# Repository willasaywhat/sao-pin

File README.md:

# SAO Pin

Quick board to provide power to an SAO without a badge. Hot glue a pin or lanyard clip on the back and wear it with pride.

Note: This is currently untested and probably doesn't work. Also uses both the DigiKey and Sparkfun libraries.

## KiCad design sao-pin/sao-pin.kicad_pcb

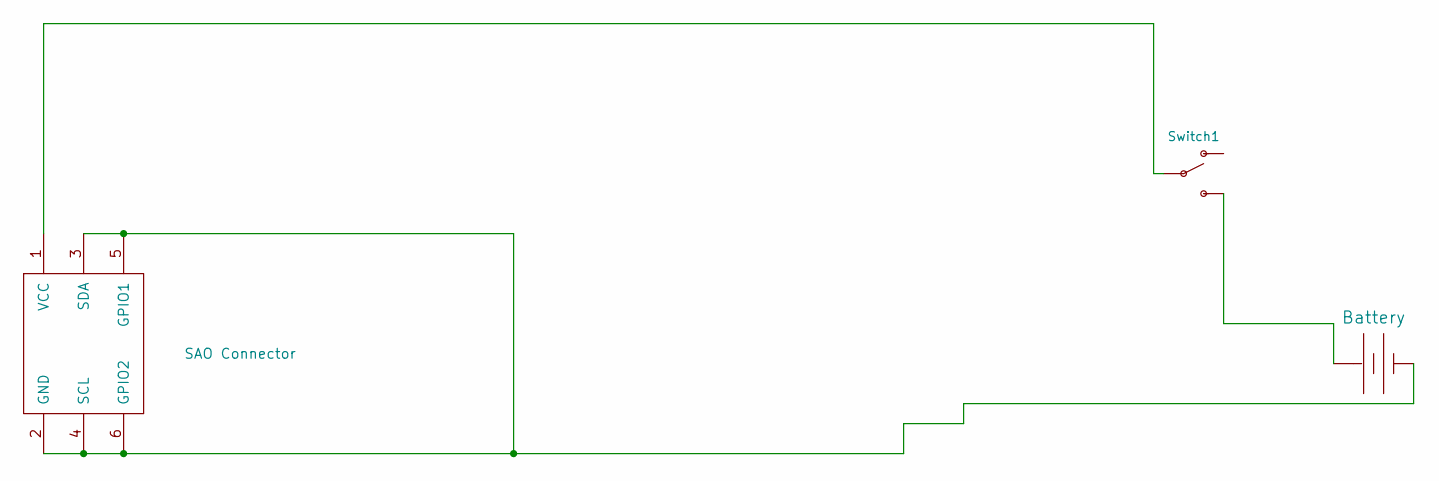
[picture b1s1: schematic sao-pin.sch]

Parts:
BT1: BATTERY-20MM_SMD; BATTCON_20MM
SAOConnector1: SAO Connector; Badgelife-SAOv169-BADGE-2x3
Switch1: SWITCH-SPDT-SMD-AYZ0202; SWITCH_DPDT_SMD_AYZ0202

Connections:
unnamed: BT1.1 (+), Switch1.3 (S)
unnamed: BT1.2 (-), SAOConnector1.2 (GND), SAOConnector1.3 (SDA), SAOConnector1.4 (SCL), SAOConnector1.5 (GPIO1), SAOConnector1.6 (GPIO2)
unnamed: SAOConnector1.1 (VCC), Switch1.2

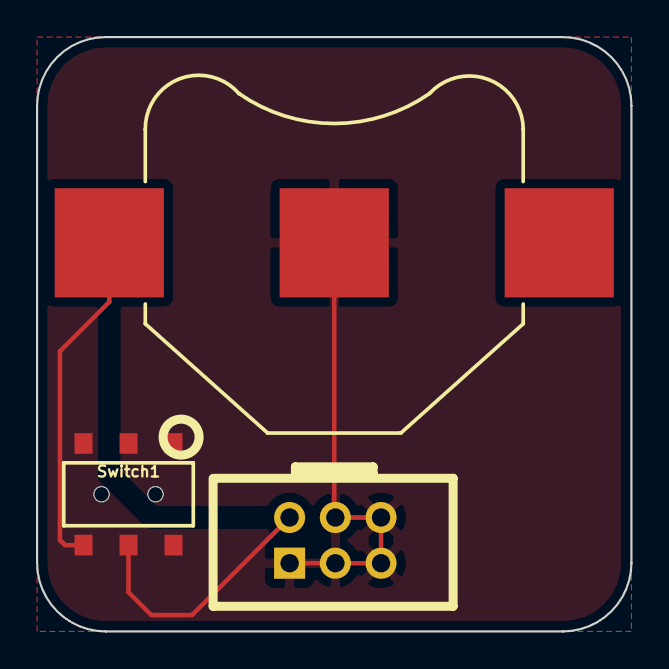
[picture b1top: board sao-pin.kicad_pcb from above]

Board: 2 copper layers, 33.0 x 33.0 mm, 3 parts (0 on the bottom side), 3 nets.
